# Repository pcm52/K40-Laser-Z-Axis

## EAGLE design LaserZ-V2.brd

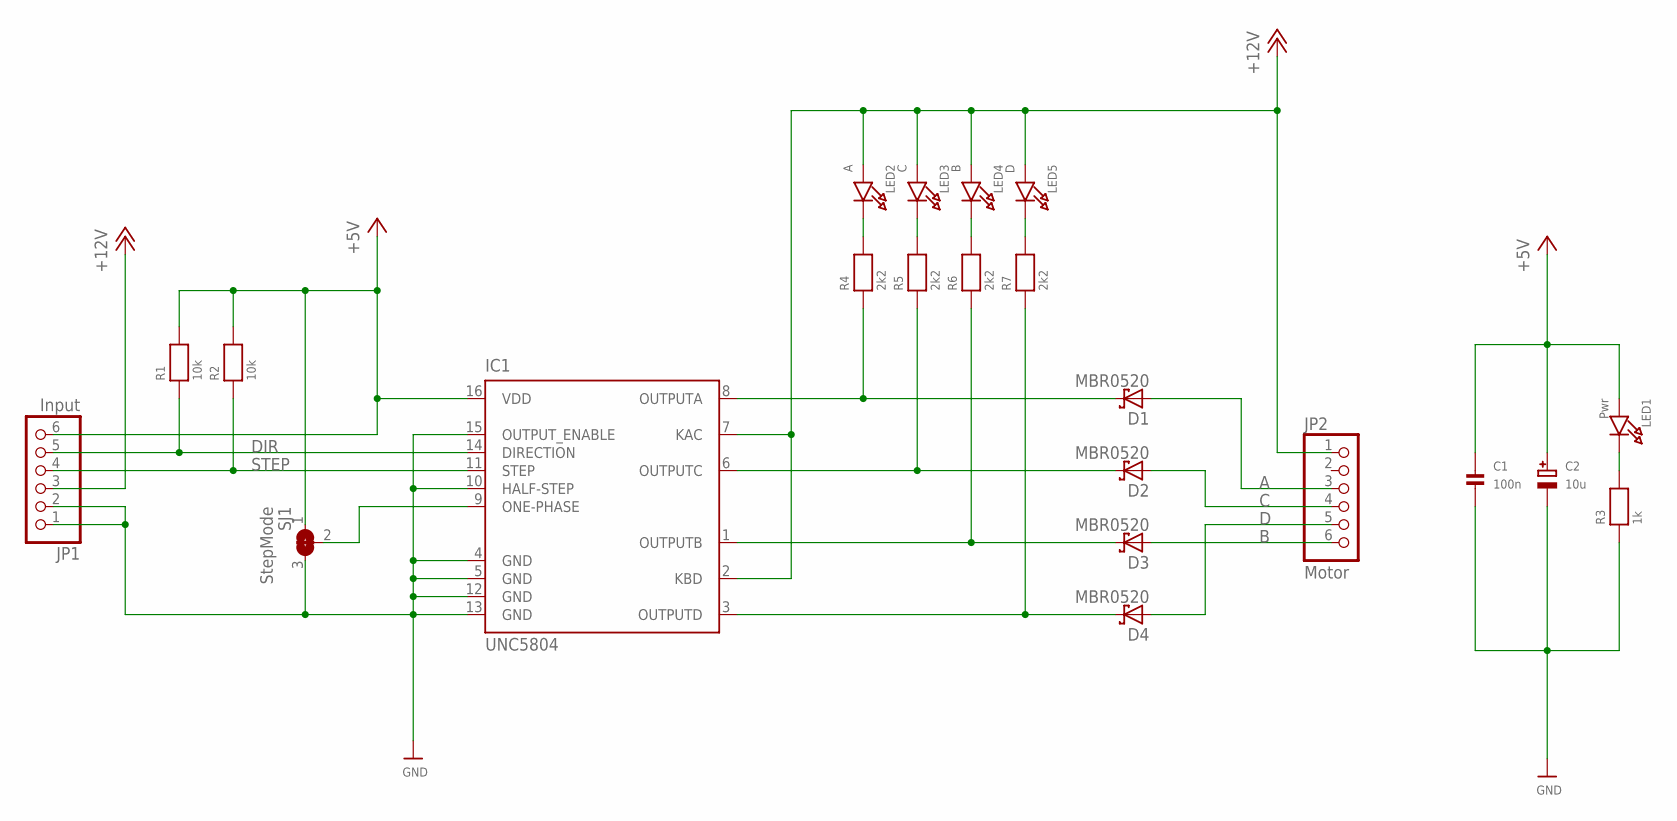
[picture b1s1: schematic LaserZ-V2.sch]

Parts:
C1: 100n; 0805
C2: 10u; EIA3216-18/A-W
D1, D2, D3, D4: MBR0520; SOD123
IC1: UNC5804; SO-16DW
JP1: Input; 1X06
JP2: Motor; 1X06
LED1: Pwr; CHIPLED_0805
LED2: A; CHIPLED_0805
LED3: C; CHIPLED_0805
LED4: B; CHIPLED_0805
LED5: D; CHIPLED_0805
R1, R2: 10k; 0805
R3: 1k; 0805
R4, R5, R6, R7: 2k2; 0805
SJ1: StepMode; SOLDERJUMPER_2WAY_OPEN_NOPASTE

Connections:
+5V: C1.1, C2.+, IC1.16 (VDD), JP1.6, LED1.A, R1.2, R2.2, SJ1.1
+12V: IC1.2 (KBD), IC1.7 (KAC), JP1.3, JP2.1, LED2.A, LED3.A, LED4.A, LED5.A
A: D1.A, JP2.3
B: D3.A, JP2.6
C: D2.A, JP2.4
D: D4.A, JP2.5
DIR: IC1.14 (DIRECTION), JP1.5, R1.1
GND: C1.2, C2.-, IC1.4 (GND), IC1.5 (GND), IC1.10 (HALF-STEP), IC1.12 (GND), IC1.13 (GND), IC1.15 (OUTPUT_ENABLE), JP1.1, JP1.2, R3.1, SJ1.3
unnamed: D1.C, IC1.8 (OUTPUTA), R4.1
unnamed: D2.C, IC1.6 (OUTPUTC), R5.1
unnamed: D3.C, IC1.1 (OUTPUTB), R6.1
unnamed: D4.C, IC1.3 (OUTPUTD), R7.1
unnamed: LED1.C, R3.2
unnamed: IC1.9 (ONE-PHASE), SJ1.2
unnamed: LED2.C, R4.2
unnamed: LED3.C, R5.2
unnamed: LED4.C, R6.2
unnamed: LED5.C, R7.2
STEP: IC1.11 (STEP), JP1.4, R2.1

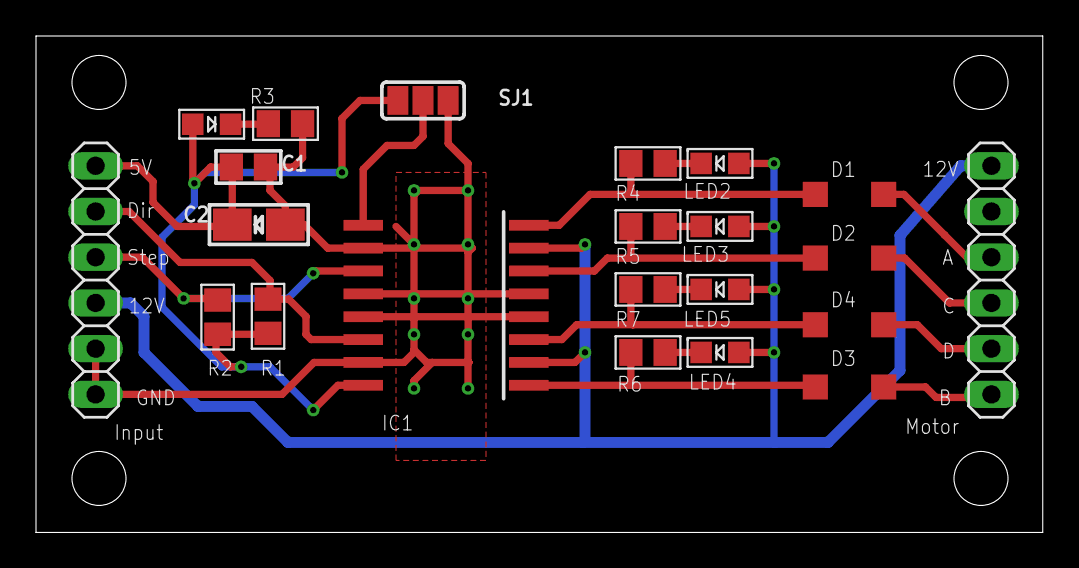
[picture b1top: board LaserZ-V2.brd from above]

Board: 2 copper layers, 55.9 x 27.6 mm, 22 parts (0 on the bottom side), 19 nets.

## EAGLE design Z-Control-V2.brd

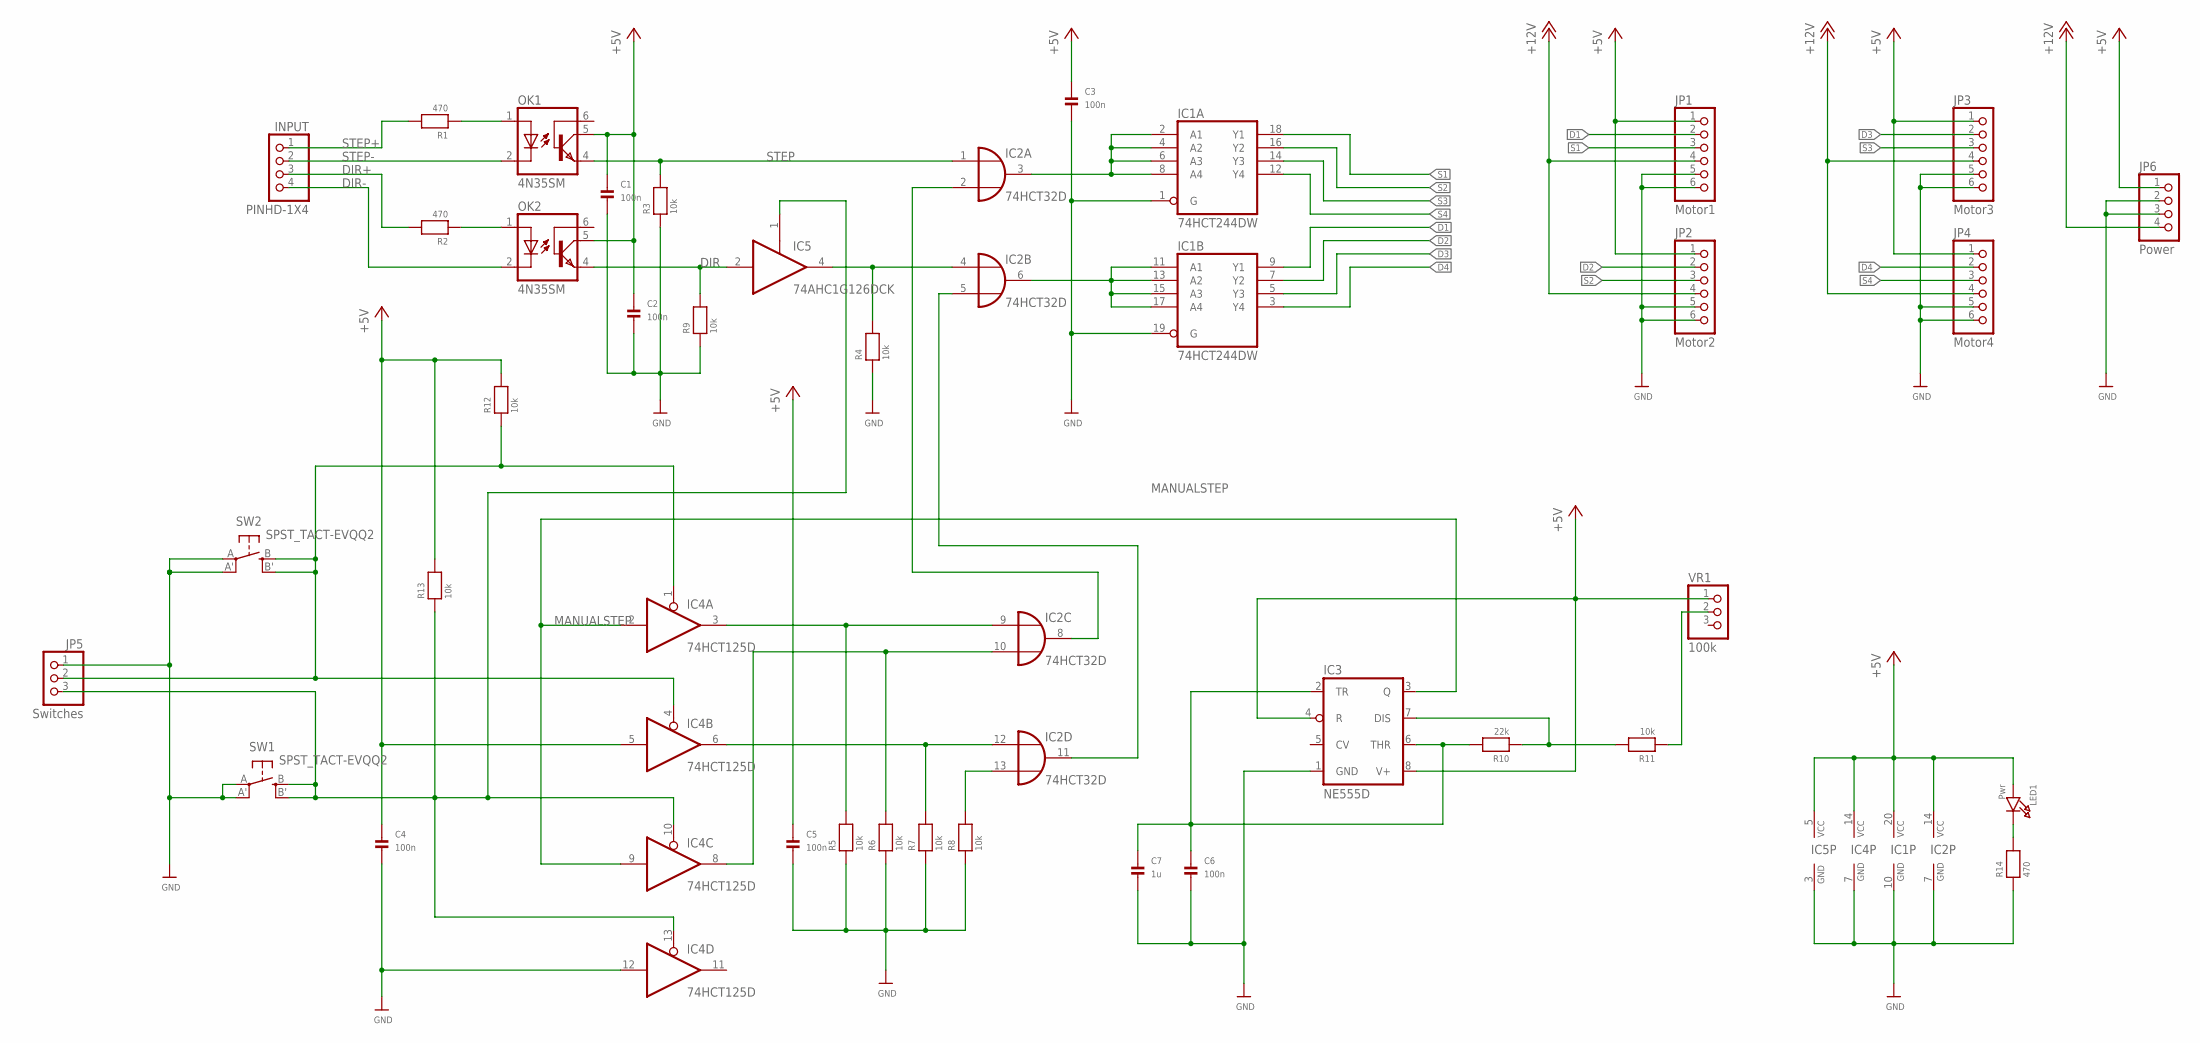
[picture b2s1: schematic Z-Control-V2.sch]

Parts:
C1, C2, C3, C4, C5, C6: 100n; _0805
C7: 1u; _0805
IC1: 74HCT244DW; SO20W
IC2: 74HCT32D; SO14
IC3: NE555D; SO08
IC4: 74HCT125D; SO14
IC5: 74AHC1G126DCK; SC70-5
INPUT: PINHD-1X4; 1X04-BIG
JP1: Motor1; 1X06
JP2: Motor2; 1X06
JP3: Motor3; 1X06
JP4: Motor4; 1X06
JP5: Switches; 1X03
JP6: Power; 1X04-BIG
LED1: Pwr; CHIPLED_0805
OK1, OK2: 4N35SM; DIL6-SMD
R1, R2, R14: 470; _0805
R3, R4, R5, R6, R7, R8, R9, R11, R12, R13: 10k; _0805
R10: 22k; _0805
SW1, SW2: SPST_TACT-EVQQ2; EVQ-Q2
VR1: 100k; 1X03_OVAL

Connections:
+5V: C1.1, C2.1, C3.1, C4.1, C5.1, IC1.20 (VCC), IC2.14 (VCC), IC3.4 (R), IC3.8 (V+), IC4.5 (I), IC4.14 (VCC), IC5.5 (VCC), JP1.1, JP2.1, JP3.1, JP4.1, JP6.1, LED1.A, OK1.5 (COL), OK2.5 (COL), R12.2, R13.2, VR1.1
+12V: JP1.4, JP2.4, JP3.4, JP4.4, JP6.4
D1: IC1.9 (Y1), JP1.2
D2: IC1.7 (Y2), JP2.2
D3: IC1.5 (Y3), JP3.2
D4: IC1.3 (Y4), JP4.2
DIR: IC5.2 (I), OK2.4 (EMI), R9.2
DIR+: INPUT.3, R2.2
DIR-: INPUT.4, OK2.2 (C)
GND: C1.2, C2.2, C3.2, C4.2, C5.2, C6.2, C7.2, IC1.1 (G), IC1.10 (GND), IC1.19 (G), IC2.7 (GND), IC3.1 (GND), IC4.7 (GND), IC4.12 (I), IC5.3 (GND), JP1.5, JP1.6, JP2.5, JP2.6, JP3.5, JP3.6, JP4.5, JP4.6, JP5.1, JP6.2, JP6.3, R3.1, R4.1, R5.1, R6.1, R7.1, R8.1, R9.1, R14.1, SW1.A, SW1.A' (P1), SW2.A, SW2.A' (P1)
MANUALSTEP: IC3.3 (Q), IC4.2 (I), IC4.9 (I)
unnamed: IC4.10 (OE), IC4.13 (OE), IC5.1 (OE), JP5.3, R13.1, SW1.B (S), SW1.B' (S1)
unnamed: IC2.13 (I1), R8.2
unnamed: OK1.1 (A), R1.1
unnamed: IC2.4 (I0), IC5.4 (O), R4.2
unnamed: OK2.1 (A), R2.1
unnamed: IC4.1 (OE), IC4.4 (OE), JP5.2, R12.1, SW2.B (S), SW2.B' (S1)
unnamed: IC1.2 (A1), IC1.4 (A2), IC1.6 (A3), IC1.8 (A4), IC2.3 (O)
unnamed: IC1.11 (A1), IC1.13 (A2), IC1.15 (A3), IC1.17 (A4), IC2.6 (O)
unnamed: IC2.9 (I0), IC4.3 (O), R5.2
unnamed: IC2.12 (I0), IC4.6 (O), R7.2
unnamed: IC2.2 (I1), IC2.8 (O)
unnamed: IC2.5 (I1), IC2.11 (O)
unnamed: IC2.10 (I1), IC4.8 (O), R6.2
unnamed: LED1.C, R14.2
unnamed: C6.1, C7.1, IC3.2 (TR), IC3.6 (THR), R10.2
unnamed: IC3.7 (DIS), R10.1, R11.2
unnamed: R11.1, VR1.2
S1: IC1.18 (Y1), JP1.3
S2: IC1.16 (Y2), JP2.3
S3: IC1.14 (Y3), JP3.3
S4: IC1.12 (Y4), JP4.3
STEP: IC2.1 (I0), OK1.4 (EMI), R3.2
STEP+: INPUT.1, R1.2
STEP-: INPUT.2, OK1.2 (C)

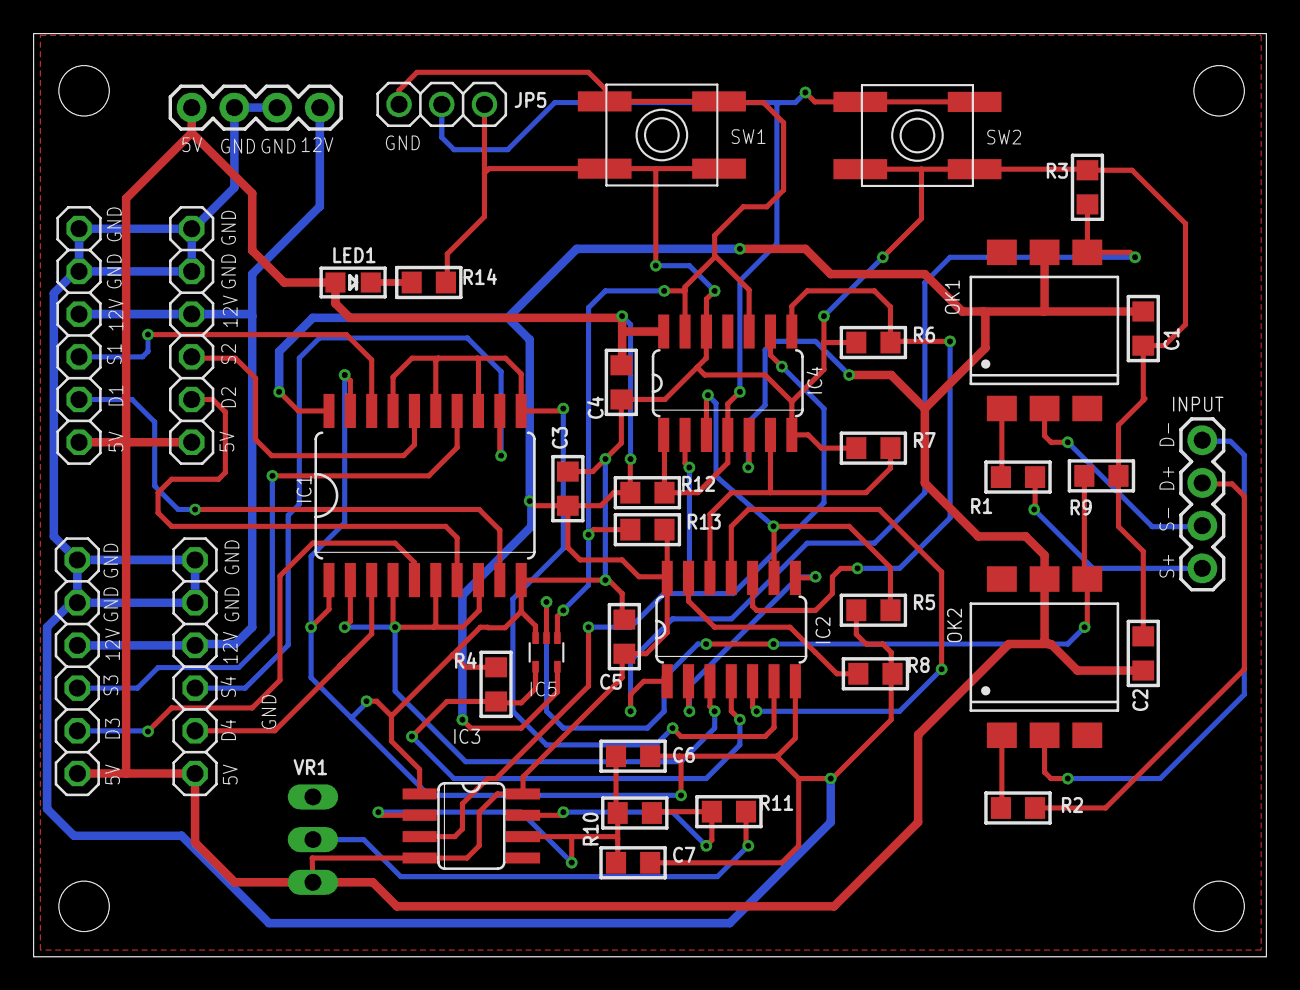
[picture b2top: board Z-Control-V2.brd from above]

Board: 2 copper layers, 73.3 x 54.9 mm, 39 parts (0 on the bottom side), 35 nets.

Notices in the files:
parts and their libraries:
microbuilder: This work is placed in the public domain, and may be freely used for commercial and non-commercial work with the following conditions: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
